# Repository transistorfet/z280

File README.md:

Z280 Computer
=============

###### *Started October 29, 2022*

A [series of] computers using the Z280, similar to the [Computie
project](https://jabberwocky.ca/projects/computie/).  The first board is a prototyping board with
the CPU's basic needs (clock/pullup resistors/etc), a 1MB Static RAM, a 1MB Flash chip, plus an
expansion bus that an Arduino can be connected to.  The bus pin assignments match Computie's
Supervisor shield, so the onboard flash chip can be programmed using the same harness as
[Computie](https://github.com/transistorfet/computie/raw/main/hardware/68k-Supervisor).

This repository uses git submodules, and can be cloned using:
```
git clone --recurse-submodules git@github.com:transistorfet/z280.git
```

Z280-SBC Revision 1
-------------------

[Schematics](https://github.com/transistorfet/z280/raw/main/hardware/Z280-SBC/Z280-SBC.pdf)

I designed the first board quickly with the idea of it being rough.  Rather than prototype the CPU
using solderless breadboards, which are prone to electrical faults, I thought I'd design a minimal
board instead, with footprints for various additional components, like memory, a compact flash card
slot, and a CPLD.  I made the mistake of using vias that were 0.4 mm total diameter, which made the
boards more expensive at JLC.  If I redesign the board, I'll probably try to use 0.45 mm vias to
avoid that.

Building the board was pretty quick and easy.  I used the supervisor shield from Computie, along
with the Arduino program
[here](https://github.com/transistorfet/z280/raw/main/software/arduino/Z280Supervisor/) to try to
feed data to the CPU live, without the memory.  I couldn't find documentation on the frequency range
of the CPU, so I used a 12 MHz crystal, which clocks the CPU at 3 MHz.  That's still too fast
though for the Arduino to assert the WAIT signal without an external flip flop to latch it.

I added the memory to the board to see if I could get the CPU executing from there instead, but it
turns out the footprint for the flash chip is upside down, and I installed the chip right way up.  I
didn't notice at first, and while trying to read from the RAM I was getting duplicate numbers in the
test pattern because the A4 address line was being held always low by the flash chip.  The flash
chip was also getting extremely hot when programming the Arduino, but not when idle, oddly enough.
Eventually I clued into the fact that the chip needed to be rotated, and was able to do that using a
hot air rework station to remove the chip.  I reused the same chip, and it seems to work, but there
are other issues with the board, and I'm a bit suspicious of it still.

Using a [logic analyzer](https://www.sparkfun.com/products/18627), I captured some signals after a
reset (I held the reset button while starting a capture and released it during the capture to get
the initial startup).  The bus cycles didn't seem to make sense for the program it should have been
executing, so I programmed the halt instruction into each byte of the first 2K of the flash and ran
it to make sure it halted pretty much right away.  It accessed memory twice before halting instead
of just once, but that might be the instruction pre-fetch (not sure yet).

I was able to use the /DS line wired to the /WAIT line to pause the CPU on the first instruction,
and then inspect the address and data buses at that point, mid bus cycle.  The address bus had the
halt instruction (0x76) on the lower byte, as did the data bus.  The lower address and data buses
are multiplexed on this CPU, and the external latches are supposed to save the address portion when
/AS is low and output them on dedicated address lines wired to the separate address pins of the
memory chips.  Since this was just after a reset, it should have been accessing address 0x0000.  The
address demultiplexing latches should have taken care of this, but it was as if they were open all
the time.  Well, I got the logic backwards on the latch enable pin, so it was was latching when the
/AS line *wasn't* asserted (low).  I must have thought it was negative logic instead of positive
logic, because the /OE pin on the same chip to enable the output is negative logic.

I was able to use one of the inverter gates for the backup clock, which wasn't populated yet, to
invert the /AS line before going into the latch enable pin (positive-logic).  That fixed the
latching issue, and it seems to execute code now, but I can't get much visibility into it yet.

I looked at the ST0-ST3 signals in particular, which output a number corresponding to the
transaction type during each bus cycle.  It seems to be running as expected, accessing memory either
cacheable (0x8) or non-cacheable (0x9), and refreshing memory (0x1).  When the CPU halts, it issues
a halt bus cycle (0x3) and then only performs refresh cycles after that.

I tried adding an EPU instruction, which is a custom Z280 instruction for accessing a coprocessor.
It uses its own transaction type, 0xD for the first word, and 0xC for all subsequent words.  Writing
that instruction into the ROM produced those codes, so it's definitely executing code.  It seemed to
sometimes halt too early though, which turned out to be the attempt at configuring the MMU.  If
there's a problem with the page table that's loaded once the MMU is enabled, it will cause "the
fatal condition" to occur, which halts the CPU.  I had a number of mistakes in the code, and the Z80
assembler I was using was producing some incorrect code.  I switched to SDCC's assembler, which
produces correct code and correct byte orders, and the MMU can now be initialized without 

With that, I set about configuring the UART according to the [Z280 Technical
Manual](https://oldcomputers.dyndns.org/public/pub/rechner/zilog/z280/manual/index.html), which also
requires Timer1 to be configured.  It worked without much trouble, and I was able to print a message
to a serial terminal.

I will need to make a more capable monitor to write to flash so that I can load and jump to code in
RAM instead so I don't need to flash the arduino and then flash the onboard chip.  I can instead
load the data over the serial terminal into ram and run it, the way I can with Computie68k.

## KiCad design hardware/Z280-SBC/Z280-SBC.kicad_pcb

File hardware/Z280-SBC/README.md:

Z280-SBC
========

Status: DO NOT BUILD (see errata)

Latest: Rev.1

### About
A single board computer with a Z280 CPU, 1MB of static RAM, and 1MB of Flash.

This board has a number of issues described in the errata, which require reworking the board.  The
flash chip needs to be upside down, and the address selection latch's operation is backwards and
needs an extra inverter gate, it or won't run code.  Also, the serial port cannot function correctly
without an external clock circuit to directly supply the UART clock because driving it indirectly
with the Z280's timer causes frequent clock glitches resulting in invalid characters being
sent/received.

[Revision 1 Notes & Errata](revisions/Z280-SBC-rev1-errata.txt)

[Revision 1 Schematic](revisions/Z280-SBC-rev1.pdf)

[Revision 1 Gerbers](revisions/Z280-SBC-rev1.zip)

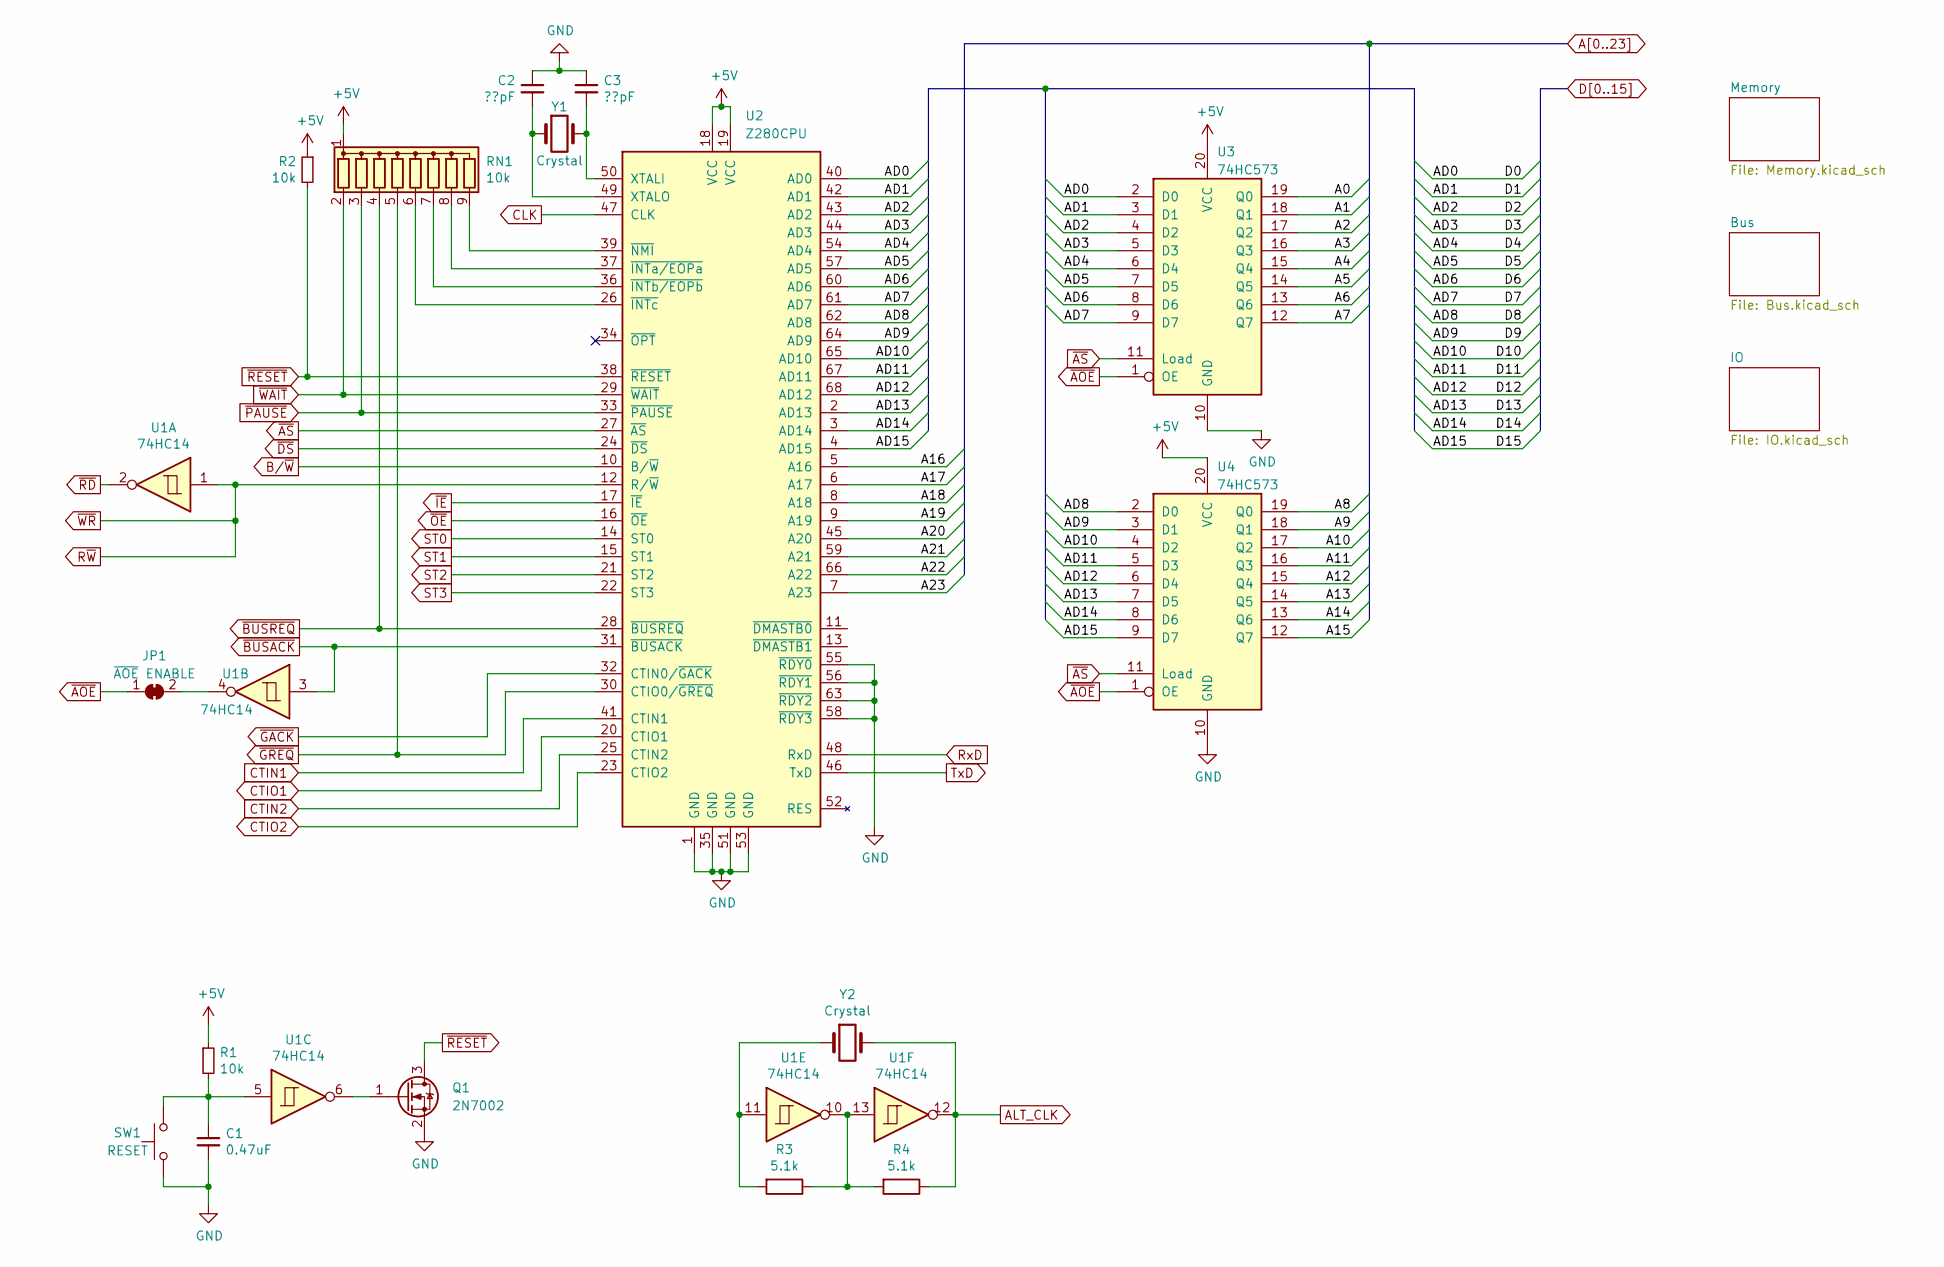
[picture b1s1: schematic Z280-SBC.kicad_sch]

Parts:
C1: 0.47uF; C_Disc_D3.0mm_W2.0mm_P2.50mm
C2, C3: ??pF; C_Disc_D3.0mm_W2.0mm_P2.50mm
JP1: ~{AOE} ENABLE; SolderJumper-2_P1.3mm_Bridged_RoundedPad1.0x1.5mm
Q1: 2N7002; SOT-23
R1, R2: 10k; R_Axial_DIN0204_L3.6mm_D1.6mm_P5.08mm_Horizontal
R3, R4: 5.1k; R_Axial_DIN0204_L3.6mm_D1.6mm_P5.08mm_Horizontal
RN1: 10k; R_Array_SIP9
SW1: RESET; SW_PUSH_6mm
U1: 74HC14; TSSOP-14_4.4x5mm_P0.65mm
U2: Z280CPU; PLCC-68_THT-Socket
U3, U4: 74HC573; TSSOP-20_4.4x6.5mm_P0.65mm
Y1, Y2: Crystal; Crystal_HC49-4H_Vertical

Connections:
+5V: R1.1, R2.1, RN1.1 (common), U2.18 (VCC), U2.19 (VCC), U3.20 (VCC), U4.20 (VCC); also elsewhere on the board
A0: U3.19 (Q0); also elsewhere on the board
A1: U3.18 (Q1); also elsewhere on the board
A2: U3.17 (Q2); also elsewhere on the board
A3: U3.16 (Q3); also elsewhere on the board
A4: U3.15 (Q4); also elsewhere on the board
A5: U3.14 (Q5); also elsewhere on the board
A6: U3.13 (Q6); also elsewhere on the board
A7: U3.12 (Q7); also elsewhere on the board
A8: U4.19 (Q0); also elsewhere on the board
A9: U4.18 (Q1); also elsewhere on the board
A10: U4.17 (Q2); also elsewhere on the board
A11: U4.16 (Q3); also elsewhere on the board
A12: U4.15 (Q4); also elsewhere on the board
A13: U4.14 (Q5); also elsewhere on the board
A14: U4.13 (Q6); also elsewhere on the board
A15: U4.12 (Q7); also elsewhere on the board
A16: U2.5 (A16); also elsewhere on the board
A17: U2.6 (A17); also elsewhere on the board
A18: U2.8 (A18); also elsewhere on the board
A19: U2.9 (A19); also elsewhere on the board
A20: U2.45 (A20); also elsewhere on the board
A21: U2.59 (A21); also elsewhere on the board
A22: U2.66 (A22); also elsewhere on the board
A23: U2.7 (A23); also elsewhere on the board
ALT_CLK: R4.1, U1.12, Y2.2; also elsewhere on the board
B/~W: U2.10 (B/~W); also elsewhere on the board
CLK: U2.47 (CLK); also elsewhere on the board
CTIN1: U2.41 (CTIN1); also elsewhere on the board
CTIN2: U2.25 (CTIN2); also elsewhere on the board
CTIO1: U2.20 (CTIO1); also elsewhere on the board
CTIO2: U2.23 (CTIO2); also elsewhere on the board
D0: U2.40 (AD0), U3.2 (D0); also elsewhere on the board
D1: U2.42 (AD1), U3.3 (D1); also elsewhere on the board
D2: U2.43 (AD2), U3.4 (D2); also elsewhere on the board
D3: U2.44 (AD3), U3.5 (D3); also elsewhere on the board
D4: U2.54 (AD4), U3.6 (D4); also elsewhere on the board
D5: U2.57 (AD5), U3.7 (D5); also elsewhere on the board
D6: U2.60 (AD6), U3.8 (D6); also elsewhere on the board
D7: U2.61 (AD7), U3.9 (D7); also elsewhere on the board
D8: U2.62 (AD8), U4.2 (D0); also elsewhere on the board
D9: U2.64 (AD9), U4.3 (D1); also elsewhere on the board
D10: U2.65 (AD10), U4.4 (D2); also elsewhere on the board
D11: U2.67 (AD11), U4.5 (D3); also elsewhere on the board
D12: U2.68 (AD12), U4.6 (D4); also elsewhere on the board
D13: U2.2 (AD13), U4.7 (D5); also elsewhere on the board
D14: U2.3 (AD14), U4.8 (D6); also elsewhere on the board
D15: U2.4 (AD15), U4.9 (D7); also elsewhere on the board
GND: C1.2, C2.1, C3.1, Q1.2 (S), SW1.1, U2.1 (GND), U2.35 (GND), U2.51 (GND), U2.53 (GND), U2.55 (~RDY0), U2.56 (~RDY1), U2.58 (~RDY3), U2.63 (~RDY2), U3.10 (GND), U4.10 (GND); also elsewhere on the board
unnamed: C1.1, R1.2, SW1.2, U1.5
unnamed: C2.2, U2.49 (XTALO), Y1.1
unnamed: C3.2, U2.50 (XTALI), Y1.2
unnamed: JP1.2 (B), U1.4
unnamed: Q1.1 (G), U1.6
unnamed: R3.1, R4.2, U1.10, U1.13
unnamed: R3.2, U1.11, Y2.1
unnamed: RN1.6 (R5), U2.26 (~INTc)
unnamed: RN1.7 (R6), U2.36 (~INTb/EOPb)
unnamed: RN1.8 (R7), U2.37 (~INTa/EOPa)
unnamed: RN1.9 (R8), U2.39 (~NMI)
RxD: U2.48 (RxD); also elsewhere on the board
R~W: U1.1, U2.12 (R/~W); also elsewhere on the board
ST0: U2.14 (ST0); also elsewhere on the board
ST1: U2.15 (ST1); also elsewhere on the board
ST2: U2.21 (ST2); also elsewhere on the board
ST3: U2.22 (ST3); also elsewhere on the board
TxD: U2.46 (TxD); also elsewhere on the board
~AOE: JP1.1 (A), U3.1 (OE), U4.1 (OE); also elsewhere on the board
~AS: U2.27 (~AS), U3.11 (Load), U4.11 (Load); also elsewhere on the board
~BUSACK: U1.3, U2.31 (~BUSACK); also elsewhere on the board
~BUSREQ: RN1.4 (R3), U2.28 (~BUSREQ); also elsewhere on the board
~DS: U2.24 (~DS); also elsewhere on the board
~GACK: U2.32 (CTIN0/~GACK); also elsewhere on the board
~GREQ: RN1.5 (R4), U2.30 (CTIO0/~GREQ); also elsewhere on the board
~IE: U2.17 (~IE); also elsewhere on the board
~OE: U2.16 (~OE); also elsewhere on the board
~PAUSE: RN1.3 (R2), U2.33 (~PAUSE); also elsewhere on the board
~RD: U1.2; also elsewhere on the board
~RESET: Q1.3 (D), R2.2, U2.38 (~RESET); also elsewhere on the board
~WAIT: RN1.2 (R1), U2.29 (~WAIT); also elsewhere on the board

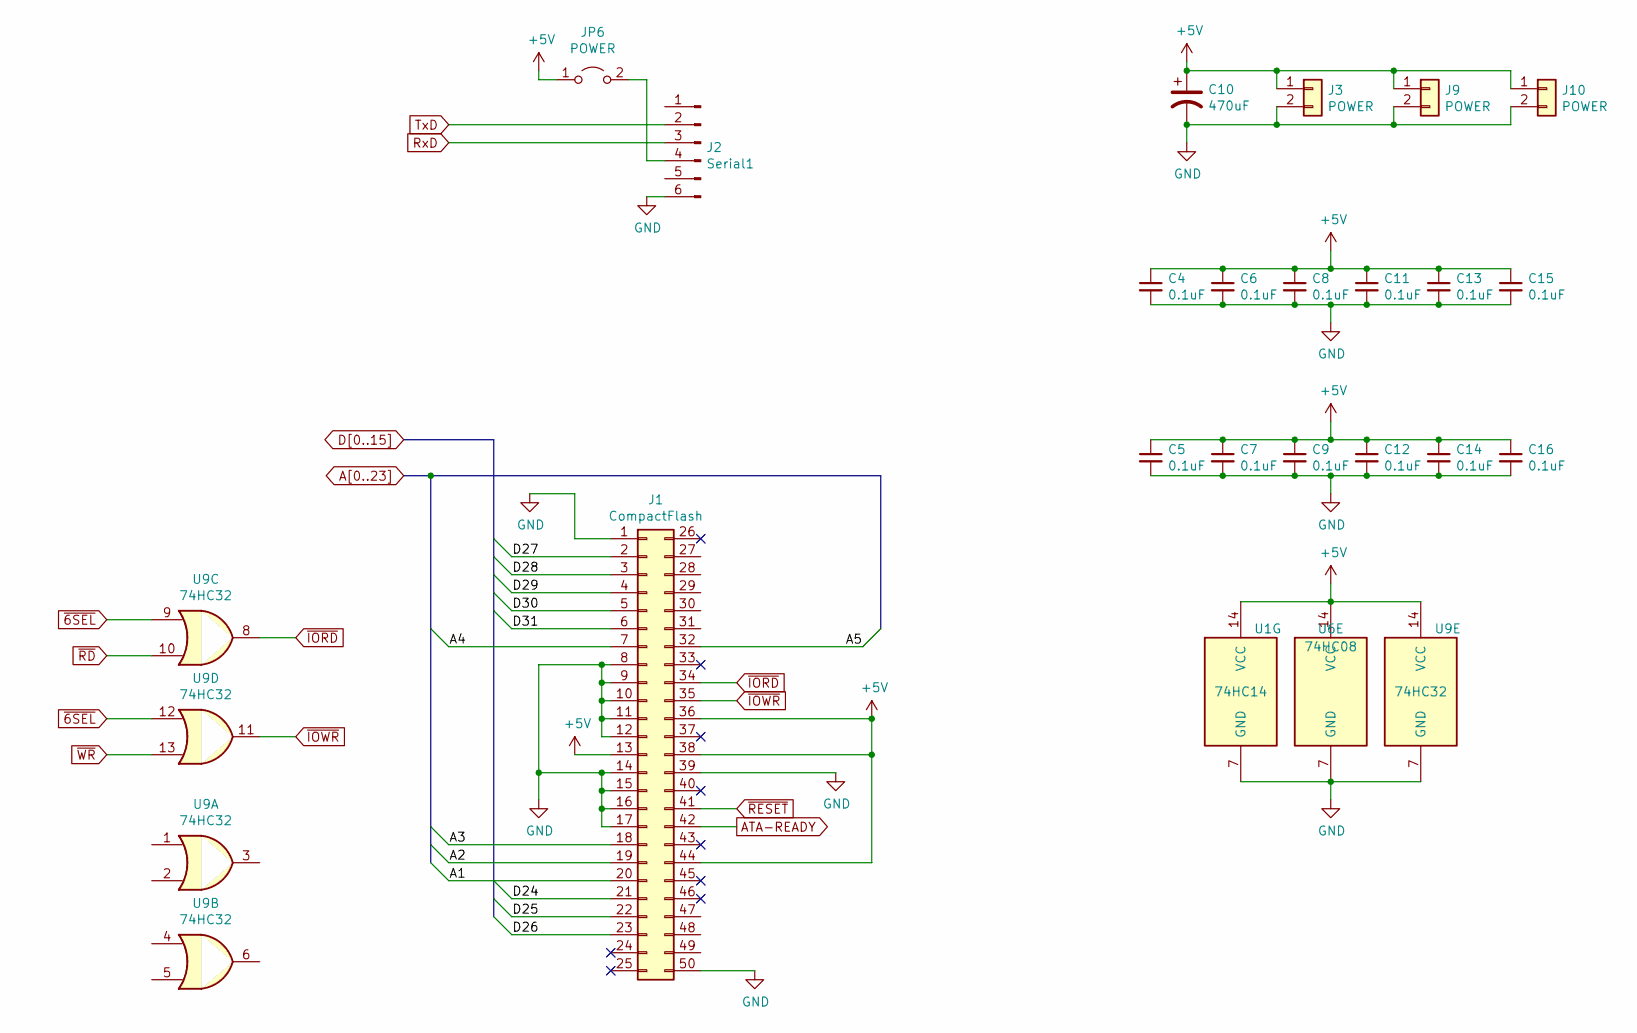
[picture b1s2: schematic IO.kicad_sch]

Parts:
C4, C5, C6, C7, C8, C9, C11, C12, C13, C14, C15, C16: 0.1uF; C_1206_3216Metric_Pad1.33x1.80mm_HandSolder
C10: 470uF; CP_Radial_D10.0mm_P5.00mm
J1: CompactFlash; CF-Card_3M_N7E50-Q516RB-40
J2: Serial1; PinHeader_1x06_P2.54mm_Vertical
J3, J9, J10: POWER; PinHeader_1x02_P2.54mm_Vertical
JP6: POWER; PinHeader_1x02_P2.54mm_Vertical
U1: 74HC14; TSSOP-14_4.4x5mm_P0.65mm
U6: 74HC08; TSSOP-14_4.4x5mm_P0.65mm
U9: 74HC32; TSSOP-14_4.4x5mm_P0.65mm

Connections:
+5V: C4.1, C5.1, C6.1, C7.1, C8.1, C9.1, C10.1, C11.1, C12.1, C13.1, C14.1, C15.1, C16.1, J1.13, J1.36, J1.38, J1.44, J3.1, J9.1, J10.1, JP6.1 (A), U1.14 (VCC), U6.14 (VCC), U9.14 (VCC); also elsewhere on the board
/IO/D24: J1.21
/IO/D25: J1.22
/IO/D26: J1.23
/IO/D27: J1.2
/IO/D28: J1.3
/IO/D29: J1.4
/IO/D30: J1.5
/IO/D31: J1.6
A1: J1.20; also elsewhere on the board
A2: J1.19; also elsewhere on the board
A3: J1.18; also elsewhere on the board
A4: J1.7; also elsewhere on the board
A5: J1.32; also elsewhere on the board
ATA-READY: J1.42; also elsewhere on the board
GND: C4.2, C5.2, C6.2, C7.2, C8.2, C9.2, C10.2, C11.2, C12.2, C13.2, C14.2, C15.2, C16.2, J1.1, J1.8, J1.9, J1.10, J1.11, J1.12, J1.14, J1.15, J1.16, J1.17, J1.39, J1.50, J2.6, J3.2, J9.2, J10.2, U1.7 (GND), U6.7 (GND), U9.7 (GND); also elsewhere on the board
unnamed: J2.4, JP6.2 (B)
RxD: J2.3; also elsewhere on the board
R~W: U9.13; also elsewhere on the board
TxD: J2.2; also elsewhere on the board
~6SEL: U9.9, U9.12; also elsewhere on the board
~IORD: J1.34, U9.8
~IOWR: J1.35, U9.11
~RD: U9.10; also elsewhere on the board
~RESET: J1.41; also elsewhere on the board

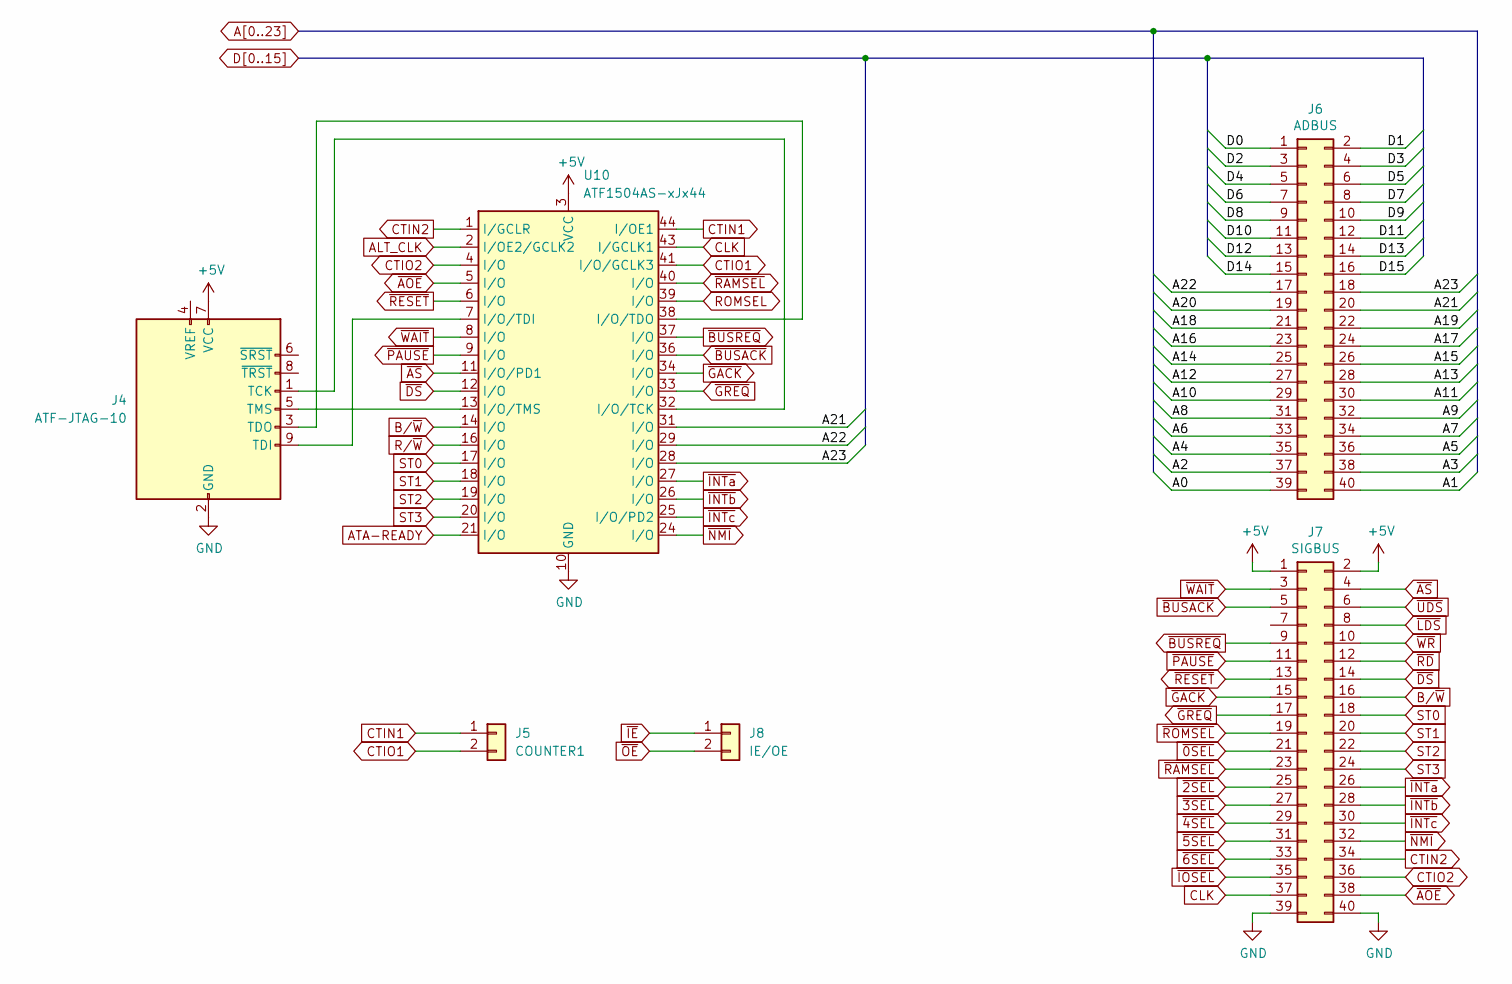
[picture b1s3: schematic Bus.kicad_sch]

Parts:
J4: ATF-JTAG-10; PinHeader_2x05_P2.54mm_Vertical
J5: COUNTER1; PinHeader_1x02_P2.54mm_Vertical
J6: ADBUS; PinHeader_2x20_P2.54mm_Vertical
J7: SIGBUS; PinHeader_2x20_P2.54mm_Vertical
J8: IE/OE; PinHeader_1x02_P2.54mm_Vertical
U10: ATF1504AS-xJx44; PLCC-44_THT-Socket

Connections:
+5V: J4.7 (VCC), J7.1, J7.2, U10.3 (VCC), U10.15 (VCC), U10.23 (VCC), U10.35 (VCC); also elsewhere on the board
A0: J6.39; also elsewhere on the board
A1: J6.40; also elsewhere on the board
A2: J6.37; also elsewhere on the board
A3: J6.38; also elsewhere on the board
A4: J6.35; also elsewhere on the board
A5: J6.36; also elsewhere on the board
A6: J6.33; also elsewhere on the board
A7: J6.34; also elsewhere on the board
A8: J6.31; also elsewhere on the board
A9: J6.32; also elsewhere on the board
A10: J6.29; also elsewhere on the board
A11: J6.30; also elsewhere on the board
A12: J6.27; also elsewhere on the board
A13: J6.28; also elsewhere on the board
A14: J6.25; also elsewhere on the board
A15: J6.26; also elsewhere on the board
A16: J6.23; also elsewhere on the board
A17: J6.24; also elsewhere on the board
A18: J6.21; also elsewhere on the board
A19: J6.22; also elsewhere on the board
A20: J6.19; also elsewhere on the board
A21: J6.20, U10.31 (I/O); also elsewhere on the board
A22: J6.17, U10.29 (I/O); also elsewhere on the board
A23: J6.18, U10.28 (I/O); also elsewhere on the board
ALT_CLK: U10.2 (I/OE2/GCLK2); also elsewhere on the board
ATA-READY: U10.21 (I/O); also elsewhere on the board
B/~W: J7.16, U10.14 (I/O); also elsewhere on the board
CLK: J7.37, U10.43 (I/GCLK1); also elsewhere on the board
CTIN1: J5.1, U10.44 (I/OE1); also elsewhere on the board
CTIN2: J7.34, U10.1 (I/GCLR); also elsewhere on the board
CTIO1: J5.2, U10.41 (I/O/GCLK3); also elsewhere on the board
CTIO2: J7.36, U10.4 (I/O); also elsewhere on the board
D0: J6.1; also elsewhere on the board
D1: J6.2; also elsewhere on the board
D2: J6.3; also elsewhere on the board
D3: J6.4; also elsewhere on the board
D4: J6.5; also elsewhere on the board
D5: J6.6; also elsewhere on the board
D6: J6.7; also elsewhere on the board
D7: J6.8; also elsewhere on the board
D8: J6.9; also elsewhere on the board
D9: J6.10; also elsewhere on the board
D10: J6.11; also elsewhere on the board
D11: J6.12; also elsewhere on the board
D12: J6.13; also elsewhere on the board
D13: J6.14; also elsewhere on the board
D14: J6.15; also elsewhere on the board
D15: J6.16; also elsewhere on the board
GND: J4.2 (GND), J4.10 (GND), J7.39, J7.40, U10.10 (GND), U10.22 (GND), U10.30 (GND), U10.42 (GND); also elsewhere on the board
unnamed: J4.1 (TCK), U10.32 (I/O/TCK)
unnamed: J4.3 (TDO), U10.38 (I/O/TDO)
unnamed: J4.5 (TMS), U10.13 (I/O/TMS)
unnamed: J4.9 (TDI), U10.7 (I/O/TDI)
ROMSEL: U10.39 (I/O)
R/~W: U10.16 (I/O)
R~W: J7.10; also elsewhere on the board
ST0: J7.18, U10.17 (I/O); also elsewhere on the board
ST1: J7.20, U10.18 (I/O); also elsewhere on the board
ST2: J7.22, U10.19 (I/O); also elsewhere on the board
ST3: J7.24, U10.20 (I/O); also elsewhere on the board
~0SEL: J7.21; also elsewhere on the board
~2SEL: J7.25; also elsewhere on the board
~3SEL: J7.27; also elsewhere on the board
~4SEL: J7.29; also elsewhere on the board
~5SEL: J7.31; also elsewhere on the board
~6SEL: J7.33; also elsewhere on the board
~AOE: J7.38, U10.5 (I/O); also elsewhere on the board
~AS: J7.4, U10.11 (I/O/PD1); also elsewhere on the board
~BUSACK: J7.5, U10.36 (I/O); also elsewhere on the board
~BUSREQ: J7.9, U10.37 (I/O); also elsewhere on the board
~DS: J7.14, U10.12 (I/O); also elsewhere on the board
~GACK: J7.15, U10.34 (I/O); also elsewhere on the board
~GREQ: J7.17, U10.33 (I/O); also elsewhere on the board
~IE: J8.1; also elsewhere on the board
~INTa: J7.26, U10.27 (I/O)
~INTb: J7.28, U10.26 (I/O)
~INTc: J7.30, U10.25 (I/O/PD2)
~IOSEL: J7.35; also elsewhere on the board
~LDS: J7.8; also elsewhere on the board
~NMI: J7.32, U10.24 (I/O)
~OE: J8.2; also elsewhere on the board
~PAUSE: J7.11, U10.9 (I/O); also elsewhere on the board
~RAMSEL: J7.23, U10.40 (I/O); also elsewhere on the board
~RD: J7.12; also elsewhere on the board
~RESET: J7.13, U10.6 (I/O); also elsewhere on the board
~ROMSEL: J7.19; also elsewhere on the board
~UDS: J7.6; also elsewhere on the board
~WAIT: J7.3, U10.8 (I/O); also elsewhere on the board

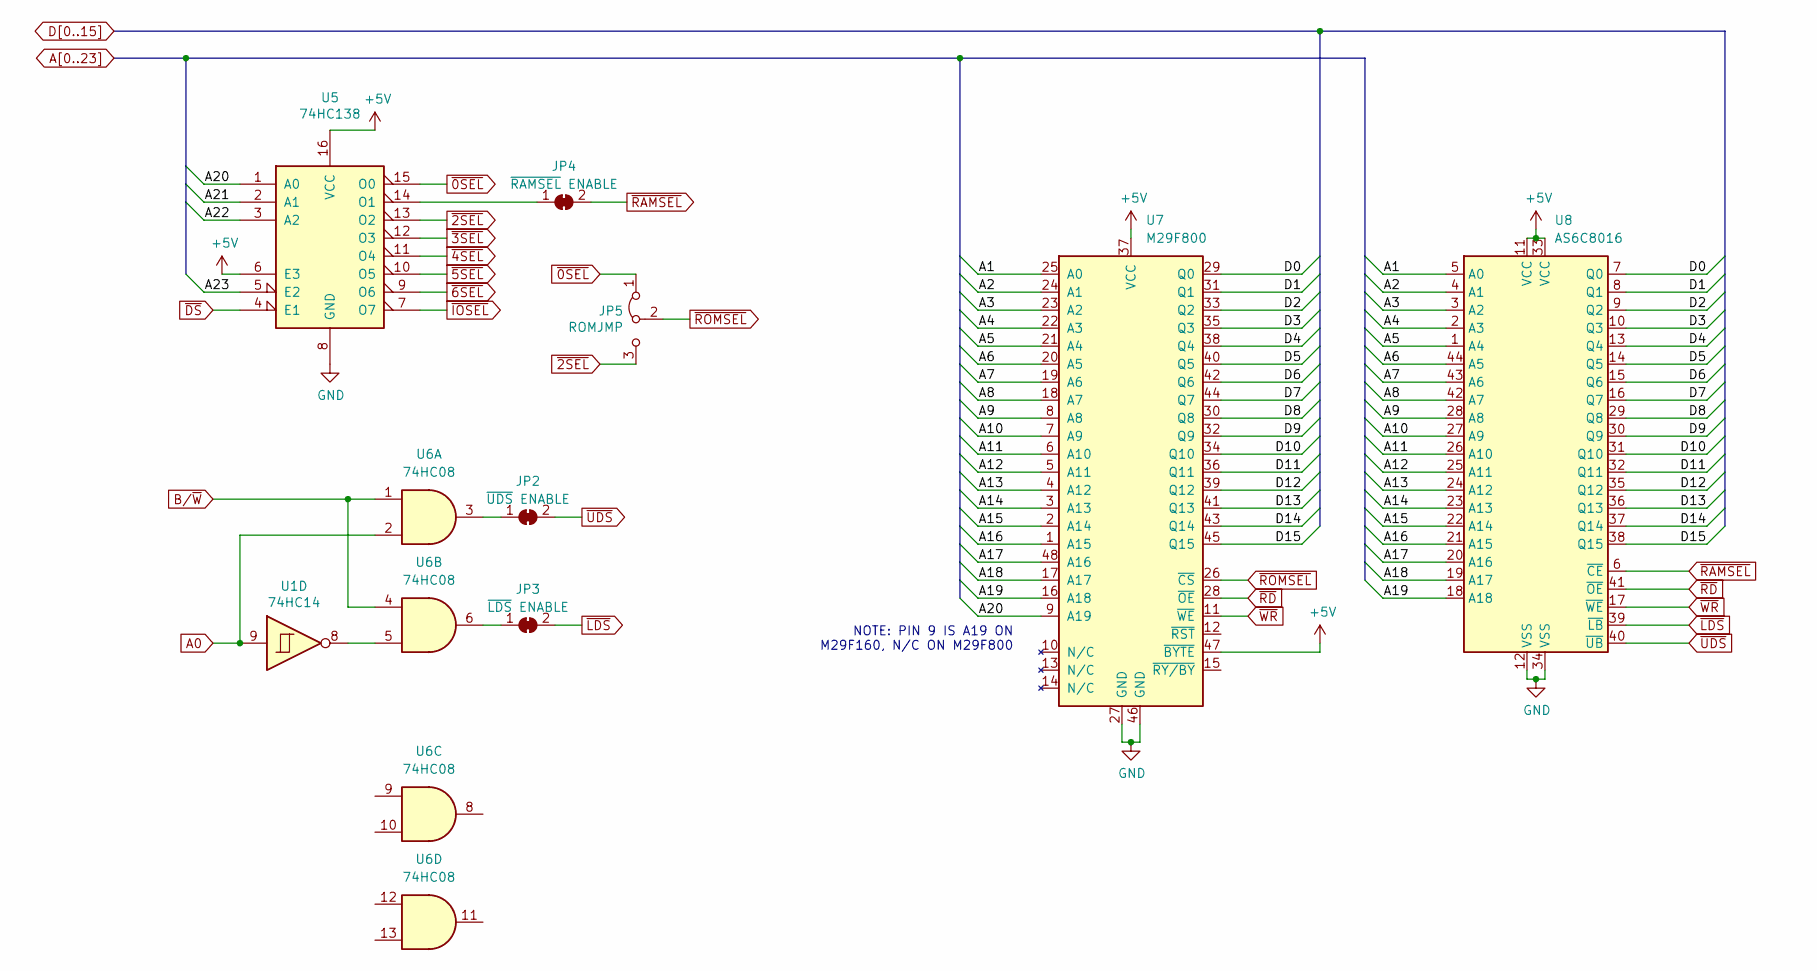
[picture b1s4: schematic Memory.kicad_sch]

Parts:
JP2: ~{UDS} ENABLE; SolderJumper-2_P1.3mm_Bridged_RoundedPad1.0x1.5mm
JP3: ~{LDS} ENABLE; SolderJumper-2_P1.3mm_Bridged_RoundedPad1.0x1.5mm
JP4: ~{RAMSEL} ENABLE; SolderJumper-2_P1.3mm_Bridged_RoundedPad1.0x1.5mm
JP5: ROMJMP; PinHeader_1x03_P2.54mm_Vertical
U1: 74HC14; TSSOP-14_4.4x5mm_P0.65mm
U5: 74HC138; TSSOP-16_4.4x5mm_P0.65mm
U6: 74HC08; TSSOP-14_4.4x5mm_P0.65mm
U7: M29F800; TSOP-I-48_18.4x12mm_P0.5mm
U8: AS6C8016; TSOP-II-44_10.16x18.41mm_P0.8mm

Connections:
+5V: U5.6 (E3), U5.16 (VCC), U7.37 (VCC), U7.47 (~BYTE), U8.11 (VCC), U8.33 (VCC); also elsewhere on the board
A0: U1.9, U6.2; also elsewhere on the board
A1: U7.25 (A0), U8.5 (A0); also elsewhere on the board
A2: U7.24 (A1), U8.4 (A1); also elsewhere on the board
A3: U7.23 (A2), U8.3 (A2); also elsewhere on the board
A4: U7.22 (A3), U8.2 (A3); also elsewhere on the board
A5: U7.21 (A4), U8.1 (A4); also elsewhere on the board
A6: U7.20 (A5), U8.44 (A5); also elsewhere on the board
A7: U7.19 (A6), U8.43 (A6); also elsewhere on the board
A8: U7.18 (A7), U8.42 (A7); also elsewhere on the board
A9: U7.8 (A8), U8.28 (A8); also elsewhere on the board
A10: U7.7 (A9), U8.27 (A9); also elsewhere on the board
A11: U7.6 (A10), U8.26 (A10); also elsewhere on the board
A12: U7.5 (A11), U8.25 (A11); also elsewhere on the board
A13: U7.4 (A12), U8.24 (A12); also elsewhere on the board
A14: U7.3 (A13), U8.23 (A13); also elsewhere on the board
A15: U7.2 (A14), U8.22 (A14); also elsewhere on the board
A16: U7.1 (A15), U8.21 (A15); also elsewhere on the board
A17: U7.48 (A16), U8.20 (A16); also elsewhere on the board
A18: U7.17 (A17), U8.19 (A17); also elsewhere on the board
A19: U7.16 (A18), U8.18 (A18); also elsewhere on the board
A20: U5.1 (A0), U7.9 (A19); also elsewhere on the board
A21: U5.2 (A1); also elsewhere on the board
A22: U5.3 (A2); also elsewhere on the board
A23: U5.5 (E2); also elsewhere on the board
B/~W: U6.1, U6.4; also elsewhere on the board
D0: U7.29 (Q0), U8.7 (Q0); also elsewhere on the board
D1: U7.31 (Q1), U8.8 (Q1); also elsewhere on the board
D2: U7.33 (Q2), U8.9 (Q2); also elsewhere on the board
D3: U7.35 (Q3), U8.10 (Q3); also elsewhere on the board
D4: U7.38 (Q4), U8.13 (Q4); also elsewhere on the board
D5: U7.40 (Q5), U8.14 (Q5); also elsewhere on the board
D6: U7.42 (Q6), U8.15 (Q6); also elsewhere on the board
D7: U7.44 (Q7), U8.16 (Q7); also elsewhere on the board
D8: U7.30 (Q8), U8.29 (Q8); also elsewhere on the board
D9: U7.32 (Q9), U8.30 (Q9); also elsewhere on the board
D10: U7.34 (Q10), U8.31 (Q10); also elsewhere on the board
D11: U7.36 (Q11), U8.32 (Q11); also elsewhere on the board
D12: U7.39 (Q12), U8.35 (Q12); also elsewhere on the board
D13: U7.41 (Q13), U8.36 (Q13); also elsewhere on the board
D14: U7.43 (Q14), U8.37 (Q14); also elsewhere on the board
D15: U7.45 (Q15), U8.38 (Q15); also elsewhere on the board
GND: U5.8 (GND), U7.27 (GND), U7.46 (GND), U8.12 (VSS), U8.34 (VSS); also elsewhere on the board
unnamed: JP2.1 (A), U6.3
unnamed: JP3.1 (A), U6.6
unnamed: JP4.1 (A), U5.14 (O1)
unnamed: U1.8, U6.5
R~W: U7.11 (~WE), U8.17 (~WE); also elsewhere on the board
~0SEL: JP5.1 (A), U5.15 (O0); also elsewhere on the board
~2SEL: JP5.3 (B), U5.13 (O2); also elsewhere on the board
~3SEL: U5.12 (O3); also elsewhere on the board
~4SEL: U5.11 (O4); also elsewhere on the board
~5SEL: U5.10 (O5); also elsewhere on the board
~6SEL: U5.9 (O6); also elsewhere on the board
~DS: U5.4 (E1); also elsewhere on the board
~IOSEL: U5.7 (O7); also elsewhere on the board
~LDS: JP3.2 (B), U8.39 (~LB); also elsewhere on the board
~RAMSEL: JP4.2 (B), U8.6 (~CE); also elsewhere on the board
~RD: U7.28 (~OE), U8.41 (~OE); also elsewhere on the board
~ROMSEL: JP5.2 (C), U7.26 (~CS); also elsewhere on the board
~UDS: JP2.2 (B), U8.40 (~UB); also elsewhere on the board

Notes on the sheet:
NOTE: PIN 9 IS A19 ON M29F160, N/C ON M29F800

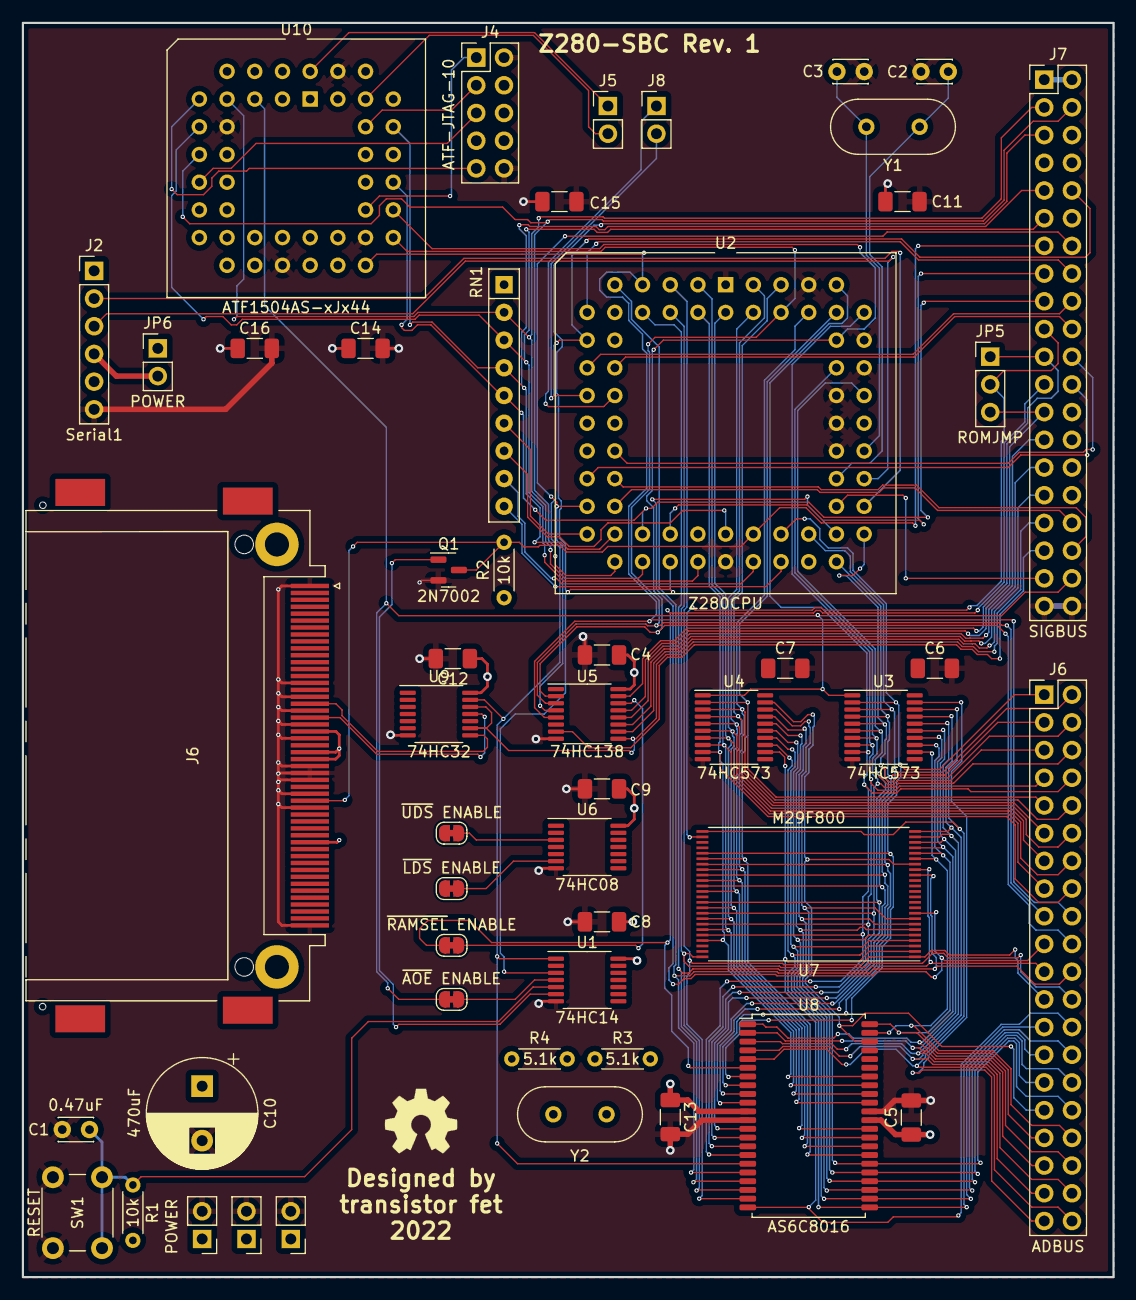
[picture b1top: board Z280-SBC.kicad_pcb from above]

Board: 4 copper layers, 100.0 x 115.0 mm, 51 parts (0 on the bottom side), 107 nets.

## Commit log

2022-11-14 Initial commit (after completing most of the design already)
    I was trying to be fairly quick with the design, rather than prototyping
    beforehand, so there are likely a lot of mistakes and issue, but this
    is intended as a prototyping board, not a usable board, so it's ok if
    it's not right the first time, as long as it can be patched.
2022-11-14 Added readme
2022-11-21 Work in progress on PCB design, address and data buses mostly connected
2022-11-26 Mostly done Rev1
2022-11-27 Rev1 - All connections completed
2022-12-02 Z280-SBC Revision 1 is complete
2022-12-24 Board is built, but there are some problems with address lines
2022-12-28 Updated and fixed some hardware issues
2022-12-28 Moved Z280 code to monitor/
2022-12-28 Got the EPU instruction to execute, which can help with debugging
2022-12-28 Added image
2022-12-29 Fixed issues with MMU and added UART transmission
2022-12-29 Separated monitor and welcome test programs
    If I can load data into ram and run it there, it makes it easier to
    test, so the monitor will, for now at least, just boot the system and
    jump to ram.
2022-12-30 Added C version
2022-12-30 Reorganized a bit
2022-12-31 Copied monitor and libc code from Computie
2023-01-02 Minor fixed from debugging
2023-01-02 Updated log
2023-01-06 Minor fixes
2023-01-09 Fixed vias and orientation of the flash chip
2023-01-11 Fixed most of the issues with Rev.1
2023-01-11 Moved the CTIN pins to output pins on the CPLD
2023-08-07 Added license
2023-08-07 Added computie-kicad-library and fixed references to point to it
2024-09-06 Added readme to board directory
